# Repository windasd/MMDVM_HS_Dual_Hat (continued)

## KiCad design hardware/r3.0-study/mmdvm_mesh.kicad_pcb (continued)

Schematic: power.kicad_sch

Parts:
BT100, BT101, BT102, BT103: 18650; BatteryHolder_Keystone_1042_1x18650; MPN 1042P; Mouser 534-1042P
C100, C135, C136, C137, C138, C141, C145, C148: 1u; C_0402_1005Metric; MPN CL05A105KA5NQNC; Mouser 187-CL05A105KA5NQNC
C101, C103, C104, C109, C110, C128, C132, C133, C134: 10u; C_0805_2012Metric; MPN CL21A106KAYNNNE; Mouser 187-CL21A106KAYNNNE
C102: 1u; C_0603_1608Metric; MPN CL10A105KB8NNNC; Mouser 187-CL10A105KB8NNNC
C105: 47n; C_0402_1005Metric; MPN CL05B473KO5NNNC; Mouser 187-CL05B473KO5NNNC
C106, C116: 4u7; C_0603_1608Metric; MPN CL10A475KO8NNNC; Mouser 187-CL10A475KO8NNNC
C107, C108, C113, C114, C129, C130: 22u; C_0805_2012Metric; MPN CL21A226MAQNNNE; Mouser 187-CL21A226MOQNNNE (Mouser EQUIV: CL21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
C111, C112, C115, C125, C126, C131, C140: 100n; C_0402_1005Metric; MPN CL05B104KO5NNNC; Mouser 187-CL05B104KO5NNNC
C117: 6n8; C_0402_1005Metric; MPN CL05B682KB5NNNC; Mouser 187-CL05B682KB5NNNC
C118: 10p; C_0402_1005Metric; MPN CL05C100JB5NNNC; Mouser 187-CL05C100JB5NNNC
C119, C120, C127: 10u; C_1206_3216Metric; MPN CL31A106KBHNNNE; Mouser 187-CL31A106KBHNNNE
C121: 22n; C_0402_1005Metric; MPN 0402B223K500NT; Mouser 187-CL05B223KB5NNNC (Mouser EQUIV: CL05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
C122, C123, C124: 22u; C_1206_3216Metric; MPN CL31A226KAHNNNE; Mouser 187-CL31A226KAHNNNE
C139: 10u; C_0603_1608Metric; MPN CL10A106MA8NRNC; Mouser 187-CL10A106MA8NRNC
C142: 68u; C_1210_3225Metric; not fitted
C143, C144: 10u; C_0402_1005Metric; MPN CL05A106MQ5NUNC; LCSC C15525
C149, C210: 4u7; C_0402_1005Metric; MPN CL05A475MP5NRNC; LCSC C23733
D100: SMAJ15CA; D_SMA; MPN SMAJ15CA; Mouser 576-SMAJ15CA
D101: orange; LED_0402_1005Metric; MPN APHHS1005SECK; Mouser 604-APHHS1005SECK
D102: BAT54; D_SOD-323; MPN BAT54HT1G; Mouser 863-BAT54HT1G
D103: 6V2; D_SOD-323; MPN MM3Z6V2T1G; LCSC C393369
D105: BAT54; D_SOD-323; MPN BAT54HT1G; not fitted
F100, F101, F102, F103: 7A; Fuse_Littelfuse-NANO2-451_453; MPN 0451007.MRL; Mouser 576-0451007.MRL
J100: USB-C (charge); USB_C_Receptacle_GCT_USB4105-xx-A_16P_TopMnt_Horizontal; MPN USB4105-GF-A; Mouser 640-USB4105-GF-A
L100: 1uH; L_Wuerth_HCI-5040; MPN 744316100; Mouser 710-744316100
L101: 1.8uH; L_Wuerth_HCI-1050; MPN 744325180; Mouser 710-744325180
L102: 1uH; L_Coilcraft_XAL4040-XXX; MPN XAL4020-102MEC; Mouser 994-XAL4020-102MEC
L103: 1.5uH; L_Coilcraft_XAL4040-XXX; MPN XAL4020-152MEC; Mouser 994-XAL4020-152MEC
Q100, Q101: CSD16340Q3; VSON-8_3.3x3.3mm_P0.65mm_NexFET; MPN CSD16340Q3; LCSC C47616
Q102, Q104: CSD25404Q3; VSON-8_3.3x3.3mm_P0.65mm_NexFET; MPN CSD25404Q3; Mouser 595-CSD25404Q3
Q103: CSD17577Q3A; VSON-8_3.3x3.3mm_P0.65mm_NexFET; MPN CSD17577Q3A; Mouser 595-CSD17577Q3A
Q105: MMBT3904; SOT-23; MPN MMBT3904; LCSC C20526
R100: 0R; R_0805_2012Metric; MPN 0805W8F0000T5E; Mouser 603-RC0805JR-070RL
R101: 0R; R_0402_1005Metric; MPN 0402WGF0000TCE; Mouser 303-0402WGF0000TCE
R102: 237R; R_0402_1005Metric; MPN 0402WGF2370TCE; LCSC C52962
R103: 5k23; R_0402_1005Metric; MPN RMCF0402FT5K23; Mouser 708-RMCF0402FT5K23
R104: 30k1; R_0402_1005Metric; MPN 0402WGF3012TCE; Mouser 303-0402WGF3012TCE
R105, R108: 2k2; R_0402_1005Metric; MPN 0402WGF2201TCE; Mouser 603-RC0402FR-072K2L
R106, R123, R127: 10k; R_0402_1005Metric; MPN 0402WGF1002TCE; Mouser 603-RC0402FR-0710KL
R107: 330R; R_0402_1005Metric; MPN 0402WGF3300TCE; Mouser 603-RC0402FR-07330RL
R109: 348k; R_0402_1005Metric; MPN 0402WGF3483TCE; Mouser 603-RC0402FR-07348KL
R110: 75k; R_0402_1005Metric; MPN 0402WGF7502TCE; Mouser 303-0402WGF7502TCE
R111: 15k; R_0402_1005Metric; MPN 0402WGF1502TCE; Mouser 303-0402WGF1502TCE
R112, R116: 732k; R_0402_1005Metric; MPN 0402WGF7323TCE; Mouser 603-RC0402FR-07732KL
R113: 80.6k; R_0402_1005Metric; MPN 0402WGF8062TCE; Mouser 603-RC0402FR-0780K6L
R114: 150k; R_0402_1005Metric; MPN 0402WGF1503TCE; Mouser 303-0402WGF1503TCE
R115: 10m; R_1206_3216Metric; MPN ERJ-8CWFR010V; Mouser 667-ERJ-8CWFR010V
R117, R120, R122: 100k; R_0402_1005Metric; MPN 0402WGF1003TCE; Mouser 603-RC0402FR-07100KL
R118: 100R; R_0402_1005Metric; MPN 0402WGF1000TCE; Mouser 603-RC0402FR-07100RL
R119: 634k; R_0402_1005Metric; MPN 0402WGF6343TCE; LCSC C270588
R121: 22k; R_0402_1005Metric; MPN 0402WGF2202TCE; LCSC C25768
R124: 10k; R_0402_1005Metric; not fitted
R126: 4k7; R_0402_1005Metric; MPN 0402WGF4701TCE; LCSC C25900
R128: 560R; R_0402_1005Metric; MPN 0402WGF5600TCE; LCSC C25126
R130, R131: 1M; R_0402_1005Metric; MPN 0402WGF1004TCE; Mouser 303-0402WGF1004TCE
SW100: POWER; SW_Push_Alps_SKRTLAE010_NarrowPad1; MPN SKRTLAE010; Mouser 688-SKRTLA
SW101: BATTERY ON/OFF; SW_CK_JS202011AQN_DPDT_Angled; MPN JS202011AQN; Mouser 611-JS202011AQN
TH100: 10k 103AT; R_0603_1608Metric; MPN NCU18XH103F60RB; Mouser 81-NCU18XH103F60RB
U100: CH224A; SSOP-10-1EP_3.9x4.9mm_P1mm_EP2.1x3.3mm; MPN CH224A; LCSC C42459160
U101: BQ25895; Texas_RTW_WQFN-24-1EP_4x4mm_P0.5mm_EP2.7x2.7mm_ThermalVias; MPN BQ25895RTWR; Mouser 595-BQ25895RTWR
U102: BQ29707; WSON-6_1.5x1.5mm_P0.5mm; MPN BQ29707DSER; Mouser 595-BQ29707DSER
U103: MAX17048; DFN-8-1EP_2x2mm_P0.5mm_EP0.9x1.3mm; MPN MAX17048G+T10; Mouser 700-MAX17048G+T10
U104: TPS61178; TPS61178_RNW; MPN TPS61178RNWR; Mouser 595-TPS61178RNWR
U105: INA226; TSSOP-10_3x3mm_P0.5mm; MPN INA226AIDGSR; Mouser 595-INA226AIDGSR
U106: LM74700; SOT-23-6; MPN LM74700QDBVRQ1; Mouser 595-LM74700QDBVRQ1
U107: TPS61022; Texas_RWU0007A_VQFN-7_2x2mm_P0.5mm; MPN TPS61022RWUR; Mouser 595-TPS61022RWUR
U108: TPS63030; WSON-10-1EP_2.5x2.5mm_P0.5mm_EP1.2x2mm; MPN TPS63030DSKR; Mouser 595-TPS63030DSKR
U109, U110: TPS7A2033; SOT-23-5; MPN TPS7A2033PDBVR; Mouser 595-TPS7A2033PDBVR
U111: STM6601CM2DDM6F; TDFN-12_2x3mm_P0.5mm; MPN STM6601CM2DDM6F; LCSC C155599
U112: LTC4412; TSOT-23-6; MPN LTC4412ES6#TRPBF; LCSC C514442

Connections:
+3V3: C138.1, C139.1, U110.5 (OUT); also elsewhere on the board
+3V3_MESH: C125.1, C136.1, C140.1, R106.2, R121.2, R123.2, U105.6 (VS), U109.5 (OUT), U111.1 (Vcc), U111.2 (~SR); also elsewhere on the board
+3V5: C133.1, C134.1, C135.1, C137.1, C144.1, R119.1, U108.1 (VOUT), U109.1 (IN), U109.3 (EN), U110.1 (IN)
+5V: C129.1, C130.1, C149.1, R116.1, U107.3 (VOUT); also elsewhere on the board
+12V_BOOST: C122.1, C123.1, C124.1, Q102.5 (D), R112.1, R115.1, U105.10 (Vin+)
+12V_SENSE: C126.2, Q103.1 (S), Q103.2 (S), Q103.3 (S), R115.2, U105.8 (Vbus), U105.9 (Vin-), U106.3 (EN), U106.6 (ANODE)
/Power/B5_FB: R116.2, R117.1, U107.4 (FB)
/Power/B5_SW: L102.2, U107.2 (SW)
/Power/B12_BST: C115.1, U104.13 (BST)
/Power/B12_CC: C117.1, R111.2
/Power/B12_COMP: C118.1, R111.1, U104.4 (COMP)
/Power/B12_DISDRV: C121.1, Q102.4 (G), R114.1, U104.9 (DISDRV)
/Power/B12_FB: R112.2, R113.1, U104.5 (FB)
/Power/B12_FREQ: R109.1, U104.1 (FREQ/SYNC)
/Power/B12_ILIM: R110.1, U104.3 (ILIMIT)
/Power/B12_SW: C115.2, L101.2, U104.7 (SW)
/Power/B12_VCC: C116.1, U104.10 (VCC)
/Power/B12_VOUT: C119.1, C120.1, C121.2, C148.1, Q102.1 (S), Q102.2 (S), Q102.3 (S), R114.2, U104.8 (VOUT)
/Power/BB_FB: R119.2, R120.1, U108.10 (FB)
/Power/BB_L1: L103.1, U108.4 (L1)
/Power/BB_L2: L103.2, U108.2 (L2)
/Power/BB_VINA: C131.1, R118.2, U108.8 (VINA)
/Power/BQ_BTST: C105.1, U101.21 (BTST)
/Power/BQ_DPDM: U101.2 (D+), U101.3 (D-)
/Power/BQ_ILIM: R102.1, U101.10 (ILIM)
/Power/BQ_PMID: C103.1, C104.1, C145.1, U101.23 (PMID)
/Power/BQ_QON: D102.2 (A), U101.12 (~QON)
/Power/BQ_STAT: D101.1 (K), U101.4 (STAT)
/Power/BQ_SW: C105.2, L100.1, U101.19 (SW), U101.20 (SW)
/Power/BQ_TS: R103.2, R104.1, TH100.1, U101.11 (TS)
/Power/BYP_GATE: Q104.4 (G), U112.5 (GATE)
/Power/CELL1+: BT100.1 (+), F100.1
/Power/CELL2+: BT101.1 (+), F101.1
/Power/CELL3+: BT102.1 (+), F102.1
/Power/CELL4+: BT103.1 (+), F103.1
/Power/CH224_VBUS: R101.2, U100.8 (VBUS)
/Power/CH224_VDD: C100.1, R100.2, U100.1 (VDD)
/Power/HOLD_ASSIST: C142.2, D105.1 (K), R124.1
/Power/HOST_PWR_EN: C142.1, R122.1, U104.11 (EN), U107.5 (EN), U110.3 (EN), U111.9 (~EN/EN)
/Power/IDEAL_GATE: Q103.4 (G), U106.5 (GATE)
/Power/IDEAL_VCAP: C126.1, U106.1 (VCAP)
/Power/ILIM_DET: Q105.1 (B), R126.2, R127.1
/Power/ILIM_X: Q105.3 (C), R102.2, R128.1
/Power/ILIM_ZEN: D103.2 (A), R126.1
/Power/PROT_BAT: C111.1, R107.2, U102.5 (BAT)
/Power/PROT_CGATE: Q101.4 (G), R131.1, SW101.5 (B)
/Power/PROT_COUT: SW101.6 (C), U102.2 (Cout)
/Power/PROT_DGATE: Q100.4 (G), R130.1, SW101.2 (B)
/Power/PROT_DOUT: SW101.1 (A), U102.3 (Dout)
/Power/PROT_MID: Q100.5 (D), Q101.5 (D)
/Power/PROT_VM: R108.2, U102.6 (V-)
/Power/STAT_LED_A: D101.2 (A), R105.2
/Power/STM_VREF: C141.1, U111.3 (Vref)
/Power/USB_CC1: J100.A5 (CC1), U100.7 (CC1)
/Power/USB_CC2: J100.B5 (CC2), U100.6 (CC2)
/Power/USB_DM: J100.A7 (D-), J100.B7 (D-), U100.5 (DM)
/Power/USB_DP: J100.A6 (D+), J100.B6 (D+), U100.4 (DP)
BTN_INT_N: R123.1, U111.11 (~INT); also elsewhere on the board
CELL+: C109.1, C110.1, C112.1, F100.2, F101.2, F102.2, F103.2, Q104.5 (D), R107.1, U101.13 (BAT), U101.14 (BAT), U103.2 (CELL), U103.3 (VDD), U112.1 (VIN); also elsewhere on the board
CELL-: BT100.2 (-), BT101.2 (-), BT102.2 (-), BT103.2 (-), C111.2, Q100.1 (S), Q100.2 (S), Q100.3 (S), R130.2, SW101.3 (C), U102.4 (VSS)
GND: C100.2, C101.2, C102.2, C103.2, C104.2, C106.2, C107.2, C108.2, C109.2, C110.2, C112.2, C113.2, C114.2, C116.2, C117.2, C118.2, C119.2, C120.2, C122.2, C123.2, C124.2, C125.2, C127.2, C128.2, C129.2, C130.2, C131.2, C132.2, C133.2, C134.2, C135.2, C136.2, C137.2, C138.2, C139.2, C140.2, C141.2, C143.2, C144.2, C145.2, C148.2, C149.2, C210.2, D100.2 (A2), D105.2 (A), J100.A1 (GND), J100.A12 (GND), J100.B1 (GND), J100.B12 (GND), J100.SH (SHIELD), Q101.1 (S), Q101.2 (S), Q101.3 (S), Q105.2 (E), R104.2, R108.1, R109.2, R110.2, R113.2, R117.2, R120.2, R122.2, R127.2, R128.2, R131.2, SW100.2, SW101.4 (A), TH100.2, U100.2 (CFG2), U100.3 (CFG3), U100.9 (CFG1), U100.11 (GND), U101.8 (OTG), U101.9 (~CE), U101.17 (PGND), U101.18 (PGND), U101.25 (PGND), U103.1 (CTG), U103.4 (GND), U103.6 (QSTRT), U103.9 (EP), U104.2 (AGND), U104.6 (PGND), U105.1 (A1), U105.2 (A0), U105.7 (GND), U106.2 (GND), U107.1 (GND), U108.3 (PGND), U108.9 (GND), U108.11 (PGND), U109.2 (GND), U110.2 (GND), U111.12 (GND), U112.2 (GND), U112.3 (CTL); also elsewhere on the board
HOST_HOLD: R124.2, U111.4 (PS_HOLD); also elsewhere on the board
PWR_BTN_N: D102.1 (K), R121.1, SW100.1, U111.6 (~PB); also elsewhere on the board
PWR_INT_N: R106.1, U101.7 (~INT), U103.5 (~ALRT); also elsewhere on the board
REGN: C106.1, R103.1, U101.22 (REGN)
SCL_AON: U101.5 (SCL), U103.7 (SCL), U105.5 (SCL); also elsewhere on the board
SDA_AON: U101.6 (SDA), U103.8 (SDA), U105.4 (SDA); also elsewhere on the board
SYS_DCIN: C127.1, Q103.5 (D), U106.4 (CATHODE); also elsewhere on the board
VBUS: C101.1, C102.1, D100.1 (A1), D103.1 (K), J100.A4 (VBUS), J100.A9 (VBUS), J100.B4 (VBUS), J100.B9 (VBUS), R100.1, R101.1, U101.1 (VBUS)
VSYS: C107.1, C108.1, C113.1, C114.1, C128.1, C132.1, C143.1, C210.1, L100.2, L101.1, L102.1, Q104.1 (S), Q104.2 (S), Q104.3 (S), R105.1, R118.1, U101.15 (SYS), U101.16 (SYS), U104.12 (VIN), U107.6 (MODE), U107.7 (VIN), U108.5 (VIN), U108.6 (EN), U108.7 (PS/SYNC), U112.6 (SENSE); also elsewhere on the board

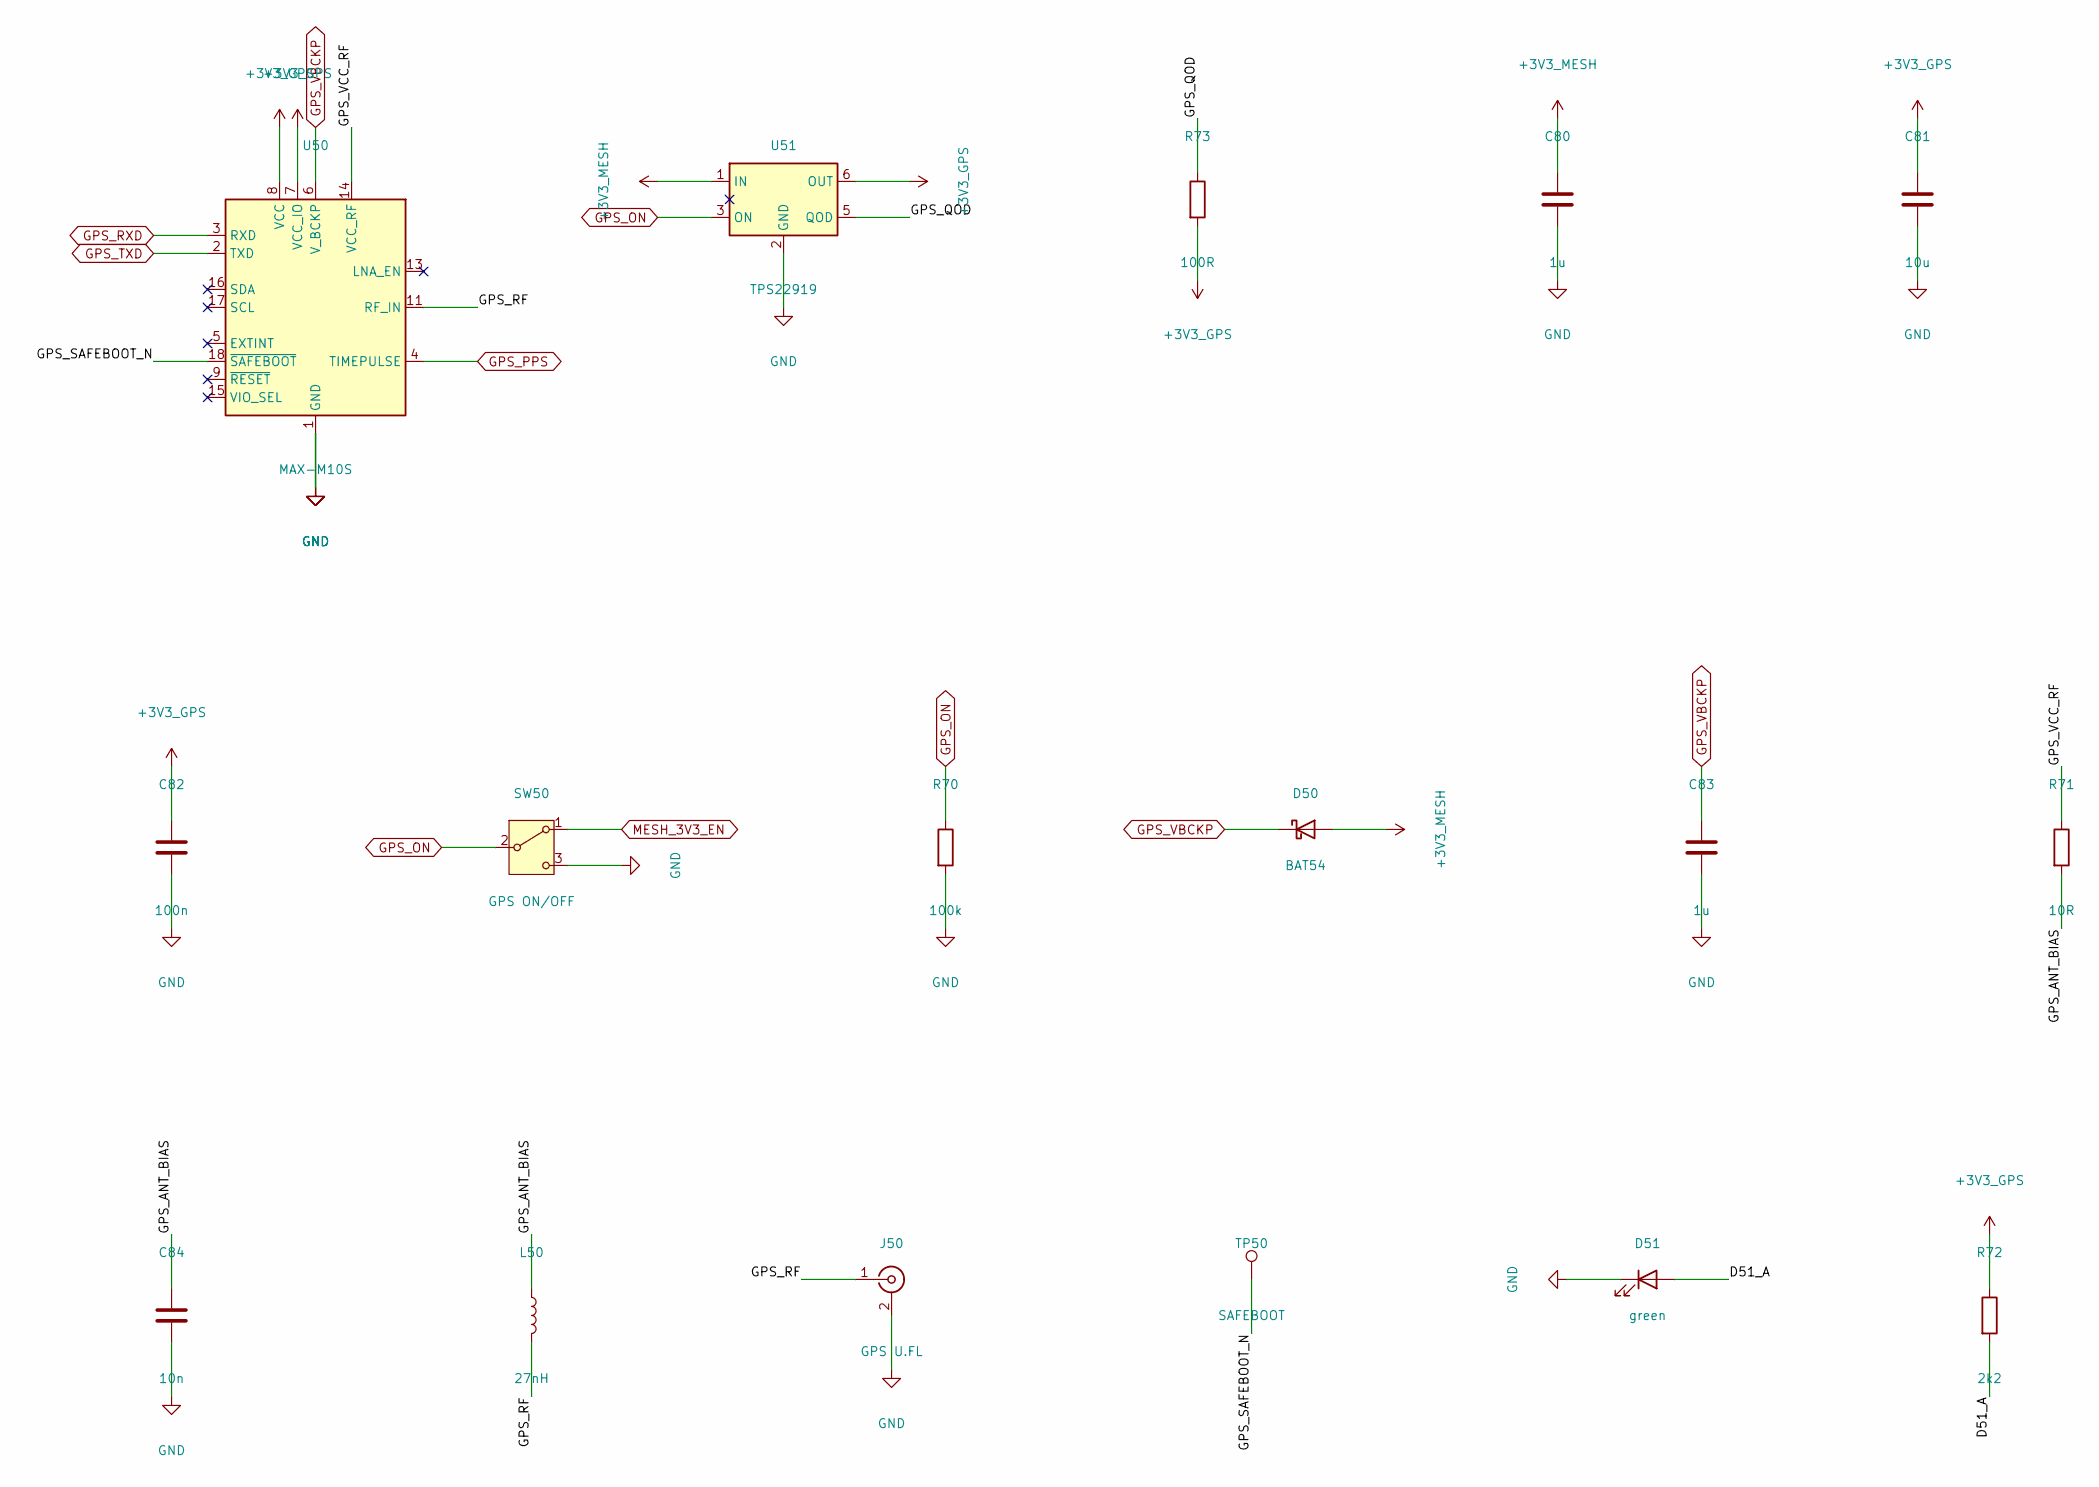
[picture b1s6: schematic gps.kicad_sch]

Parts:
C80, C83: 1u; C_0402_1005Metric; MPN CL05A105KA5NQNC; Mouser 187-CL05A105KA5NQNC
C81: 10u; C_0603_1608Metric; MPN CL10A106MA8NRNC; Mouser 187-CL10A106MA8NRNC
C82: 100n; C_0402_1005Metric; MPN CL05B104KO5NNNC; Mouser 187-CL05B104KO5NNNC
C84: 10n; C_0402_1005Metric; MPN CL05B103KB5NNNC; Mouser 187-CL05B103KB5NNNC
D50: BAT54; D_SOD-323; MPN BAT54HT1G; Mouser 863-BAT54HT1G
D51: green; LED_0402_1005Metric; MPN APHHS1005LCGCK; Mouser 604-APHHS1005CGCK
J50: GPS U.FL; U.FL_Hirose_U.FL-R-SMT-1_Vertical; MPN U.FL-R-SMT-1(10); Mouser 798-U.FL-R-SMT-110
L50: 27nH; L_0402_1005Metric; MPN LQW15AN27NG80D; Mouser 81-LQW15AN27NG80D
R70: 100k; R_0402_1005Metric; MPN 0402WGF1003TCE; Mouser 603-RC0402FR-07100KL
R71: 10R; R_0603_1608Metric; MPN ESR03EZPF10R0; Mouser 755-ESR03EZPF10R0
R72: 2k2; R_0402_1005Metric; MPN 0402WGF2201TCE; Mouser 603-RC0402FR-072K2L
R73: 100R; R_0402_1005Metric; MPN 0402WGF1000TCE; Mouser 603-RC0402FR-07100RL
SW50: GPS ON/OFF; SW_SPDT_PCM12_EdgeMount; MPN PCM12SMTR; Mouser 611-PCM12SMTR
TP50: SAFEBOOT; TestPoint_Pad_D1.0mm
U50: MAX-M10S; ublox_MAX; MPN MAX-M10S-00B; Mouser 377-MAX-M10S-00B
U51: TPS22919; SOT-363_SC-70-6; MPN TPS22919DCKR; Mouser 595-TPS22919DCKR

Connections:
+3V3_GPS: C81.1, C82.1, R72.1, R73.2, U50.7 (VCC_IO), U50.8 (VCC), U51.6 (OUT)
+3V3_MESH: C80.1, D50.2 (A), U51.1 (IN); also elsewhere on the board
/GPS/D51_A: D51.2 (A), R72.2
/GPS/GPS_ANT_BIAS: C84.1, L50.1, R71.2
/GPS/GPS_QOD: R73.1, U51.5 (QOD)
/GPS/GPS_RF: J50.1 (In), L50.2, U50.11 (RF_IN)
/GPS/GPS_SAFEBOOT_N: TP50.1, U50.18 (~SAFEBOOT)
/GPS/GPS_VCC_RF: R71.1, U50.14 (VCC_RF)
GND: C80.2, C81.2, C82.2, C83.2, C84.2, D51.1 (K), J50.2 (Ext), R70.2, SW50.3 (C), U50.1 (GND), U50.10 (GND), U50.12 (GND), U51.2 (GND); also elsewhere on the board
GPS_ON: R70.1, SW50.2 (B), U51.3 (ON); also elsewhere on the board
GPS_PPS: U50.4 (TIMEPULSE); also elsewhere on the board
GPS_RXD: U50.3 (RXD); also elsewhere on the board
GPS_TXD: U50.2 (TXD); also elsewhere on the board
GPS_VBCKP: C83.1, D50.1 (K), U50.6 (V_BCKP)
MESH_3V3_EN: SW50.1 (A); also elsewhere on the board
